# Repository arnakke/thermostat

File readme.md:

Intelligent Thermostat
----------------------
The thermostat should control room temperature based on the time of day and the location of residents. Thermostats will be connected together in rooms and homes, so if a room has multiple radiators, they will all have the same temperature set point, and if all residents have left the home, the temperature in all rooms will be lowered. Whether residents are home will be determined based on the location of their smartphones. 
Rooms should be able to have different temperatures during day and night, so that eg. the temperature is lowered in the living room during night and in the bedroom during day.  
The goal is a “set and forget” device, meaning that ideally you will never have to touch the app or the thermostats after initial configuration. That means it should also include air out detection, to stop heating when windows or doors are open. This detection could be augmented by utilizing outdoor temperature measurements from an online weather service.  
The device might also include a photovoltaic cell (or alternatively a peltier element) to reduce or eliminate battery changes.  
The design philosophy is to have as simple a user experience as possible. The thermostat should be easily installable and simple to configure, with no central control unit.

While there are a lot of similar products in the market, this thermostat sets itself apart by having:
* Centralized control without a central control unit
* Potentially a much lower price point than comparable systems (low price bill of materials)
* A design goal of being simple, unintrusive and “set and forget” (in contrast to big control panels, painful programming, manually turning on/off remotely and similar features)
* Open software and hardware design

### Preliminary requirements:
1. Thermostat unit should be mountable on Danfoss type  RA radiator valve
2. Thermostat unit should be able to partially open the radiator valve in at least 20 steps
3. Thermostat unit should be able to completely close the radiator valve
4. Thermostat unit should be able to measure temperature in a resolution of 0.1 °C with +/- 0.5 °C precision in the range 0 - 30 °C
5. Thermostat unit should be able to regulate the temperature to within +/- 0.5 °C of the set point, measured as a 5 minute average (doors and windows closed, moderate ventilation)
6. Thermostat unit should have a battery life of minimum 6 months
7. Thermostat units communicate over wifi
8. The control app should be able to run on Android 4.4
9. Residents should be warned of low battery in a thermostat unit through the control app
10. Temperature can be set per room in the control app, with different settings for night and day
11. The hours for day and night can be configured in the control app
12. The time should be set automatically in the thermostat unit
13. Changing the temperature in a room changes the set point of all units belonging to that room
14. Changing the temperature in a room should take effect on all thermostat units after max. 5 minutes
15. When all registered resident smartphones are away from the home, the temperature is lowered in all rooms relatively to the distance to the nearest resident (beeline)
16. The temperature set point will never go below 5 °C
17. A registered resident smartphone that doesn’t report its position should be considered to approach the home at a configurable speed with default 50 km/h
18. Thermostat units should be able to detect an open window based on change in temperature, possibly taking into consideration outdoor temperature (to be specified further)

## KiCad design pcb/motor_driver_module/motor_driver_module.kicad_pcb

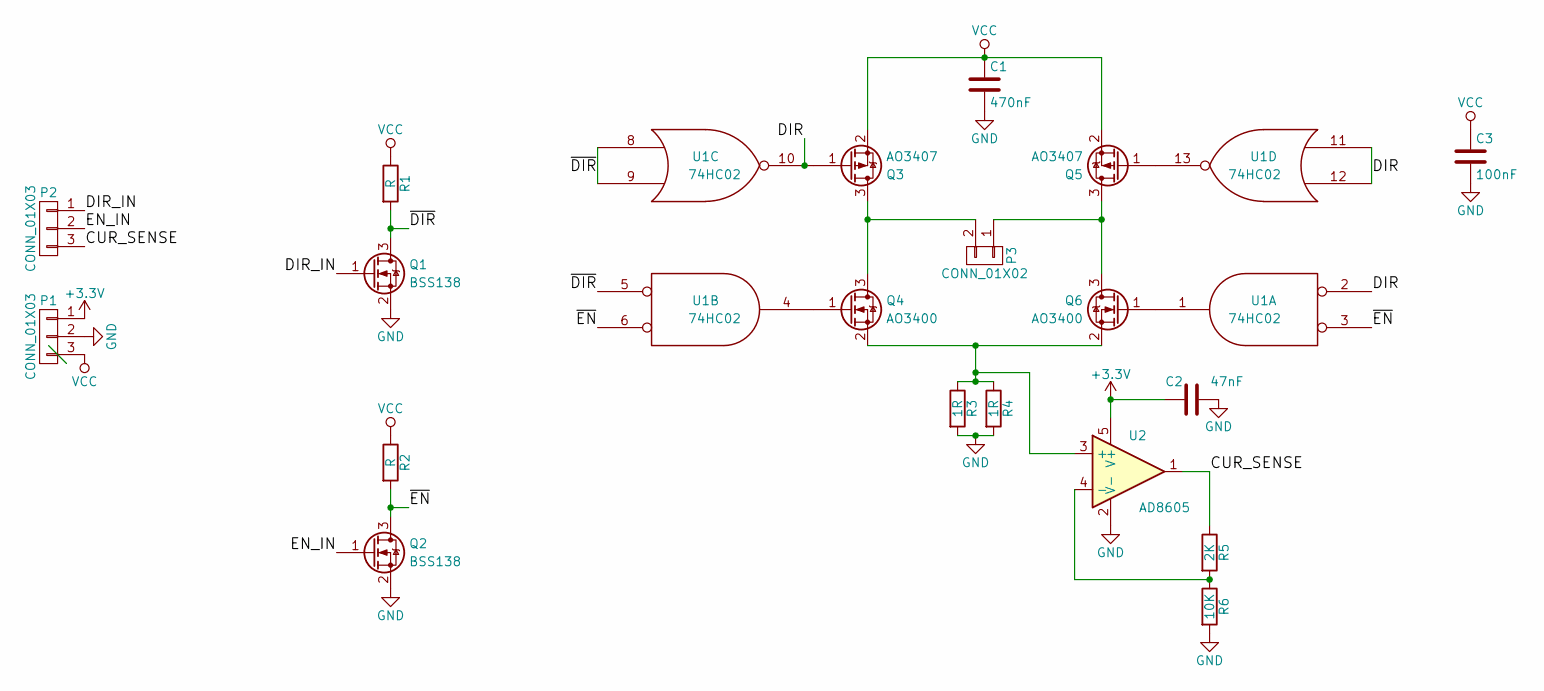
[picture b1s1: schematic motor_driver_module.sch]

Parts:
C1: 470nF; C_0805
C2: 47nF; C_0805
C3: 100nF; C_0805
P1, P2: CONN_01X03; Pin_Header_Straight_1x03
P3: CONN_01X02; Pin_Header_Straight_1x02
Q1, Q2: BSS138; SOT-23
Q3, Q5: AO3407; SOT-23
Q4, Q6: AO3400; SOT-23
R1, R2: R; R_0805
R3, R4: 1R; R_0805
R5: 2K; R_0805
R6: 10K; R_0805
U1: 74HC02; SOIC-14_3.9x8.7mm_Pitch1.27mm
U2: AD8605; SOT-23-5

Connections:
+3V3: C2.2, P1.1, U2.5 (V+)
/CUR_SENSE: P2.3, R5.1, U2.1
/DIR: U1.2, U1.11, U1.12
/DIR_IN: P2.1, Q1.1 (G)
/EN_IN: P2.2, Q2.1 (G)
/~DIR: Q1.3 (D), R1.2, U1.5, U1.8, U1.9
/~EN: Q2.3 (D), R2.2, U1.3, U1.6
GND: C1.2, C2.1, C3.2, P1.2, Q1.2 (S), Q2.2 (S), R3.2, R4.2, R6.2, U1.7 (GND), U2.2 (V-)
unnamed: P3.1, Q5.3 (D), Q6.3 (D)
unnamed: P3.2, Q3.3 (D), Q4.3 (D)
unnamed: Q3.1 (G), U1.10
unnamed: Q4.1 (G), U1.4
unnamed: Q4.2 (S), Q6.2 (S), R3.1, R4.1, U2.3 (+)
unnamed: Q5.1 (G), U1.13
unnamed: Q6.1 (G), U1.1
unnamed: R5.2, R6.1, U2.4 (-)
VCC: C1.1, C3.1, P1.3, Q3.2 (S), Q5.2 (S), R1.1, R2.1, U1.14 (VCC)

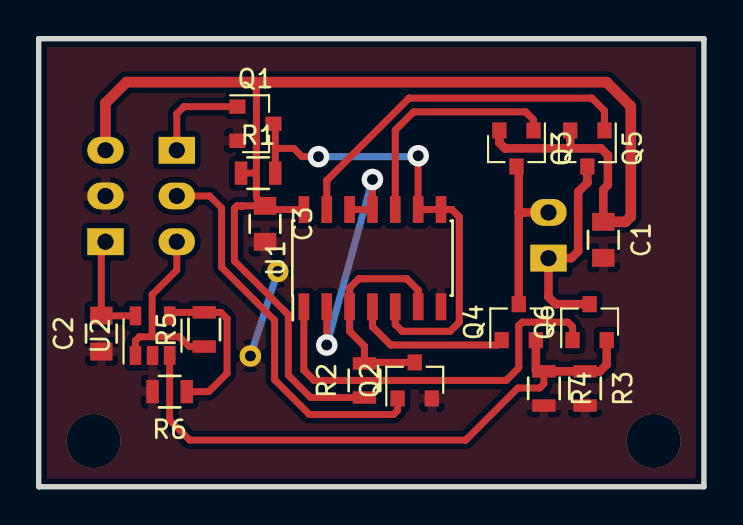
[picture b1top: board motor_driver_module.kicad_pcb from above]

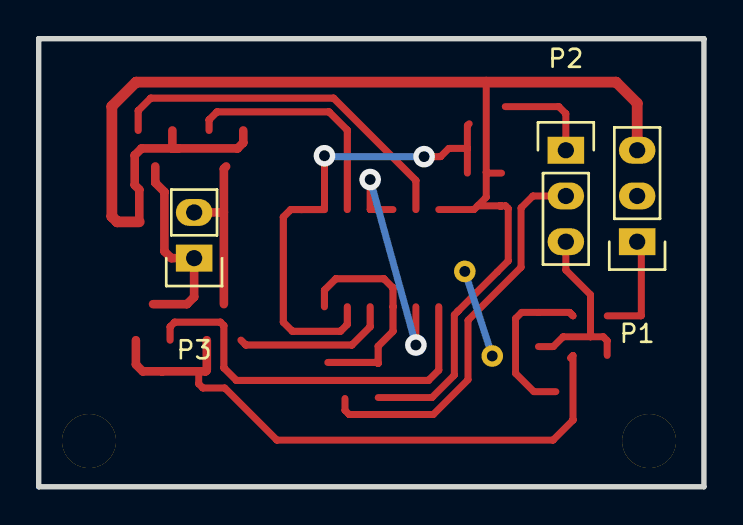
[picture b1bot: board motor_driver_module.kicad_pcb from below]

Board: 2 copper layers, 37.0 x 24.9 mm, 20 parts (3 on the bottom side), 17 nets.

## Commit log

2017-09-12 Initial project description
2017-09-12 Numbered preliminary requirements and additional requirement
2017-10-13 Initial chassis design
2017-10-13 Empty ESP-IDF project
2017-10-13 Empty Android project
2017-10-24 Added motor driver PCB prototype
2017-10-24 Ignore Eclipse project files
2017-10-24 Added ADC class
2017-10-24 Added temperature sensor class
